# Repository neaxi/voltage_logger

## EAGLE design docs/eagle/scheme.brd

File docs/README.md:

# Voltage logger
CS50 Video demo: https://youtu.be/C_FzpJQzrRs
    
    

# What & Why 
Our goal is to have graphable discharge data when load testing UPS batteries. Target UPS systems for this project are using max. 4 batteries configuration (like APC RBC25), so the whole design is affected by this cap.  
Therefore, we're performing voltage logging of accumulator pack up to 59 V, ie. 4x fully charged Pb or LiFePo4 batteries in a series.  
Permanent log (.csv) is stored on the SD card and currently measurred values are available via serial interface (microUSB).

# Operations
**Usage**
1. connect GND to the accumulator pack GND
2. connect lead #4 to the accumulator pack (+)  
3. connect leads #1, #2, #3 to individual cells
4. turn on the logger via PWR switch
    - the logger will always start in "setup" mode
5. use calibrated voltmeter to measure cell #1 voltage and use calibration potentiometer on the logger to adjust measured values
6. flip the SD switch into (1), to enter the "measurement" mode
    - different time intervals
    - SD card logging

**Timing**
- 0.5 s - ADS sampling
- 1 s - LCD refresh
- 2 s - CLI printout in "setup" mode
- 20 s - CLI printout in "measurement" mode
- 120 s - interval with which the data are written on the SD card

# Technical
**Electronics**
- ESP32 + [MicroPython](https://docs.micropython.org/en/latest/esp32/tutorial/intro.html)
  - `python -m esptool --port COM12 --baud 921600 write_flash 0x1000 esp32-20210902-v1.17.bin`
- ADS 1115 ADC
  - 16 bit, 4 channel, channel V<sub>max</sub> = V<sub>dd</sub>, I2C (72 = 0x48)
  - has to be powered by 5V in our case (or voltage divider has to be adjusted)
  - we're measuring all cells against common ground and getting individual cell voltages via subtraction
  - by default the measured voltage is obtained by `RAW * 6.144 / 32768` (`6.144` is the gain; `32768` is the 2^16 range). The transformation is included into polynomial correction formulas in our case. Calibration measurements are available in the documentation.
  - ADC GND is connected to "both" grounds - power source GND and step down GND
    - this partially bypasses the power switch as even when turned off the power buss for digital part has active voltage, but low enough to avoid activating anything
    - V<sub>src</sub> -> V<sub>pwrbus</sub>: 57 V -> 0.83 V; 30 V -> 0.48 V; 10 V -> 0.07 V
  - **Calibration**
    - ADC raw value measurements were taken for each channel on 10, 15, 20, 25, 30, 35, 40, 45, 50, 55, 58 volts.
    - third-degree polynominal formulas were derived from the measurements and are being applied on the values reported by the ADC to get better precision (absolute deviation below 0.05 V)
    - offset is also added to the measured value to ensure deviation is symmetrical/centered around the real value

- SD card reader
  - SPI, reader is picky on what SD card it accepts
    - user is notified if the logger can't write on the SD
  - has to be connected to VSPI (id 2, pins 18,23,19) to prevent conflict with [GPIO12 (MTDI bootstraping)](https://docs.espressif.com/projects/esp-idf/en/release-v4.0/api-reference/peripherals/sd_pullup_requirements.html#mtdi-strapping-pin)
  - data are buffered and written based on time interval to prevent excesive writes with each individual measurement  

- 4 channel voltage divider
  - reducing 0-60 V to 0-5V range
  - 110 kΩ : 10 kΩ ([Divider calc](https://ohmslawcalculator.com/voltage-divider-calculator))

**Interface**
- haptic
  - BTN1 - Power off/on
  - BTN2 - Enable/Disable SD write 
  - P1 potentiometer - fine adjustment (+-0.5 V range; 0.1 V steps) of the measured voltage based on a manual check with calibrated multimeter
- LCD
    - I2C, 2x16 (or 20x4) chars, provides current values and instructions
    - 20x4:
        - default I2C address = 39 (0x27)
    - custom LCD char guide https://clach04.github.io/lcdchargen/
        
- UART/Serial data line
    - to allow terminal output and logging (PuTTY). Speed: 115200
    - connected into FT232/CH430/CP2102 USB
    - RX/TX lines are opto-isolated
        - USB interface is powered from the USB hub
        - no electrical connection with the measured circuit preventing PC/laptop/USB hub from contact with the cells/pack
        - isolated by 6N137 (10 Mbit/s interface)

**Protections and power supply**
- The logger feeds from the measured pack. Inaccuracies introduced by this approach were evaluated as insignificant for our purpose (17 mA draw on average).
- Step down (H6201 based?) is powered from the whole pack/highest voltage. Death of individual cell should not affect overall operation.
- Fuse (630mA) + Zener diode (62V) connected before step down 
    - In case of overvoltage the Zener breaks and causes sufficient amperage to burn the fuse.
    - Connected before step down convertor.
- Step down is set to 5V and powers all the electronics.

# Future 
**TBD / not finished**
- [x] - subtract voltages from each other to get net voltages staright from the logger
- [x] - debug switch to change behavior for development/troubleshooting  
  - different LCD and CLI printout

**Possible future features**
- [ ] - replace fuses with PTC/Polyfuse
  - suitable RC circuit would have to be designed due to slow polyfuse react times
- [ ] - use ALRT/RDY pin on ADS1115 to verify it's ready 
- [x] - automatic selection of the power line based on the max. voltage  
  - DONE, handled in analog

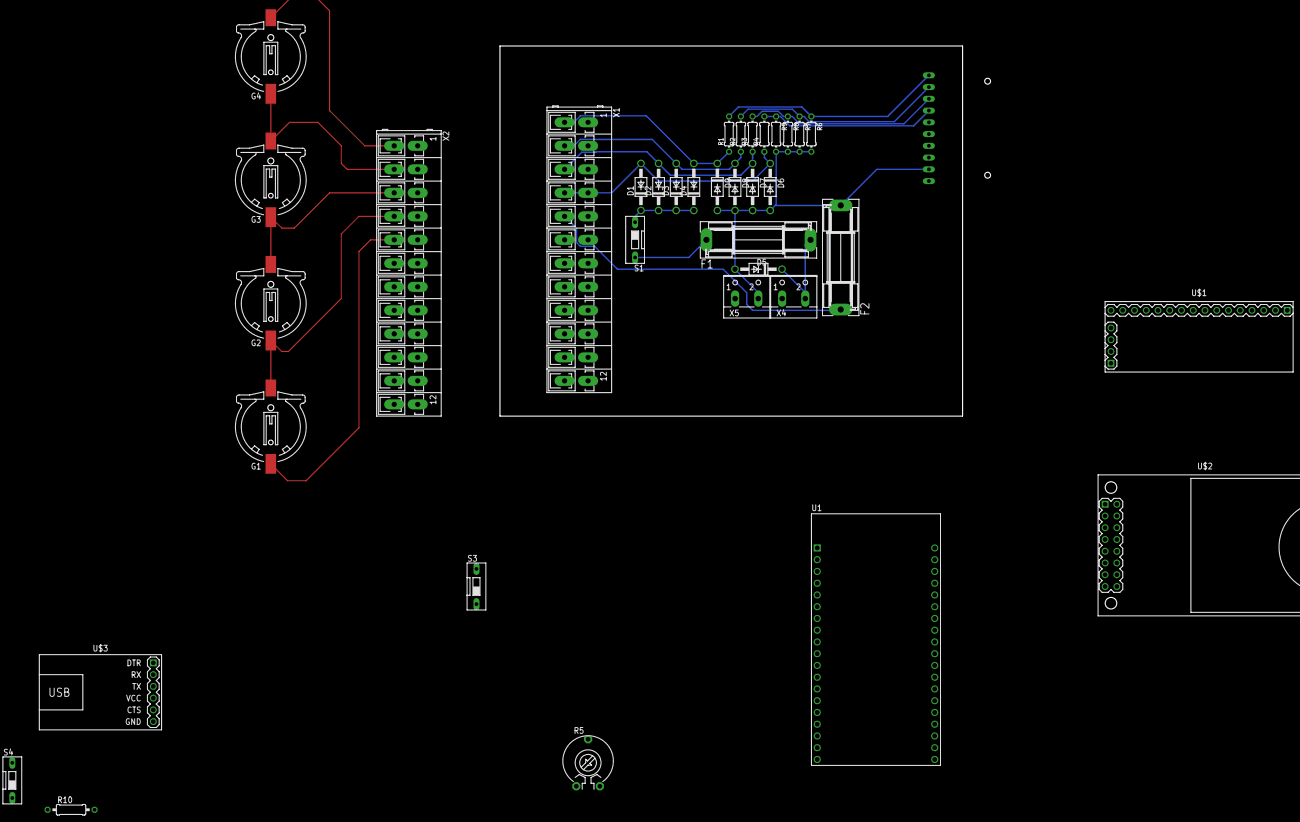
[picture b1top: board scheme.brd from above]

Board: 2 copper layers, 100.0 x 80.0 mm, 37 parts (1 on the bottom side), 30 nets.

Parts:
D1, D2, D3, D4, D6, D7, D8, D9: 1N4004; DO41-10
D5: DO41Z10
F1, F2: FUSESH22,5; SH22,5
G1, G2, G3, G4: CH291-1220LF
IO1: 10PIN
R1, R2, R3, R4: 110k; 0204/7
R5: PT-10
R6, R7, R8, R9: 10k; 0204/7
R10: 0207/10
S1, S3, S4: DS-01
U1: ESP32-DEVKITC-32D; MODULE_ESP32-DEVKITC-32D
U$1: LCD-I2C-CONVERTER
U$2: CARD-SD-ADAPTER
U$3: USB-SERIAL-FT232R
X1, X2: 236-412
X4, X5: W237-102

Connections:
3V3: U1.1, U$2.3
+5V: R10.2, S3.1, U1.19, U$1.J1.1, U$1.J1.4, U$1.J2.16, U$2.1, U$2.5, X5.1
GND: D5.A, D6.A, D7.A, D8.A, D9.A, F2.2, IO1.2, R5.1, R6.2, R7.2, R8.2, R9.2, S4.2, X4.1, X5.2
unnamed: U1.23, U$2.9
unnamed: IO1.7, R4.2, R9.1
unnamed: U1.28, U$2.11
unnamed: U1.27, U$2.13
unnamed: U1.29, U$2.7
unnamed: IO1.8, R3.2, R8.1
unnamed: IO1.9, R2.2, R7.1
unnamed: IO1.10, R1.2, R6.1
unnamed: R5.3, U1.7
unnamed: D1.C, D2.C, D3.C, D4.C, S1.1
unnamed: F1.1, S1.2
unnamed: D5.C, F1.2, X4.2
unnamed: G1.+, G2.-, X2.4@1, X2.4@2
unnamed: D4.A, D9.C, R1.1, X1.1@1
unnamed: G3.+, G4.-, X2.2@1
unnamed: G4.+, X2.1@1
unnamed: D3.A, D8.C, R2.1, X1.2@1
unnamed: F2.1, X1.5@1
unnamed: D2.A, D7.C, R3.1, X1.3@1
unnamed: D1.A, D6.C, R4.1, X1.4@1, X1.4@2
unnamed: G1.-, X2.5@1
unnamed: G2.+, G3.-, X2.3@1
unnamed: S3.2, U$1.J2.15
unnamed: R5.2, R10.1
unnamed: S4.1, U1.32
SCL: IO1.3, U1.22, U$1.J1.3
SDA: IO1.4, U1.25, U$1.J1.2

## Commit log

2021-09-21 boilerplate
2021-09-23 Readme draft
2021-11-21 proof of concept code for sd, ads, lcd, uart
2021-11-21 first working demo
    initializes hardware
    measeuremnt loop with LCD info
    demo was used to obtain calibration data
2021-11-21 documentation update
2021-11-22 corrected ADC calibrations
2021-11-25 threads
    - display (cli,lcd) and measurements in sparate threads
    - measured values are averaged accross ADS_KEPT_VALUES
2021-11-30 async redesign - coro 1 - ads measurement
2021-11-30 async redesign - coro 2 - data prep
2021-11-30 async redesign - coro 3 - LCD voltage update
2021-11-30 async redesign - coro 3 - CLI print + removed locking
2021-11-30 async redesign - coro 5 - pot/sw I/O
2021-12-01 async redesign - coro 6 - SD handling
2021-12-01 voltage correction steps modifications
2021-12-10 SD write and LCD msgs
2021-12-29 improve SD handling and user coms
2021-12-29 readme update
2021-12-29 cleanup
2022-01-05 voltage subtractions and debug button
2022-02-09 write buffer when going back to setup
    SD write as standalone function, to enable calling outside of the async
    minor user interface printout tweaks

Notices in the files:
parts and their libraries:
i2c_lcd_convertor: Released under the Creative Commons Attribution 4.0 International License: http://creativecommons.org/licenses/by/4.0
